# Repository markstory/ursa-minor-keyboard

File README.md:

# Ursa Minor Keyboard

This repository contains design and schematic files for the usra-minor keyboard design.

## Handwired

This directory contains the design files used to create the initial prototype of the tryptris keyboard.
You can find a design/build guide on my blog:

* [Part 1](http://mark-story.com/posts/view/building-a-split-keyboard-part-1)
* [Part 2](http://mark-story.com/posts/view/building-a-split-keyboard-part-2)
* [Part 3](http://mark-story.com/posts/view/building-a-split-keyboard-part-3)

## v01

This directory contains the first drafts of the PCB based build. I've completed
design on two variants. Both have been printed and tested. A few defects were
found in the `v01/bling` board. These defects have been corrected. I've posted
a [longer article on the design and production](http://mark-story.com/posts/view/designing-my-first-keyboard-pcb).

### Notable Features

* **Single MCU** - Instead of dual microcontrollers, this design uses only
  a microcontroller and IO expander pairing. This lets more cost effective
  components be used and only requires a single flash operation when updating
  firmware.
* **Thumb Arc** The thumb cluster follows the thumb's natural arc, and all keys
  are reachable in 1u of space. Unlike many thumb arcs, this one requires no
  reaching under the palm.
* **No Frills, or Frills** The base model has a simple stripped down keyboard.
  It has no lights, no encoders, just 58 switches and wires. The bling model
  includes support for per-key RGB.

### v01/base

**🖨Printed, ✅Tested**

This is a basic board design. It has has no frills and a smaller parts list. The intention is that it used caseless with self-adhesive feet, or directly on a desk.

### v01/bling

**🖨Printed, ✅Tested**

This design builds on caseless foundatin of the `v01/base` and adds per-key RGB lighting via RGB matrix drivers over I2C. Like the base board it is intended to be used caseless.

### v01/bling-case

**🏗Work In Progress**

This board is a distinct design from `v01/bling` & `v01/base`. It is intended to be used with a switch plate and hollow body case.

### Firmware

Firmware for the `v01/base` and `v01/bling` can be found [in my QMK fork][https://github.com/markstory/qmk_firmare/tree/ursa-minor-v1].

## FAQ

**Why Ursa Minor?**

The keypad shape and thumb arc remind me of [Ursa Minor](https://en.wikipedia.org/wiki/Ursa_Minor).

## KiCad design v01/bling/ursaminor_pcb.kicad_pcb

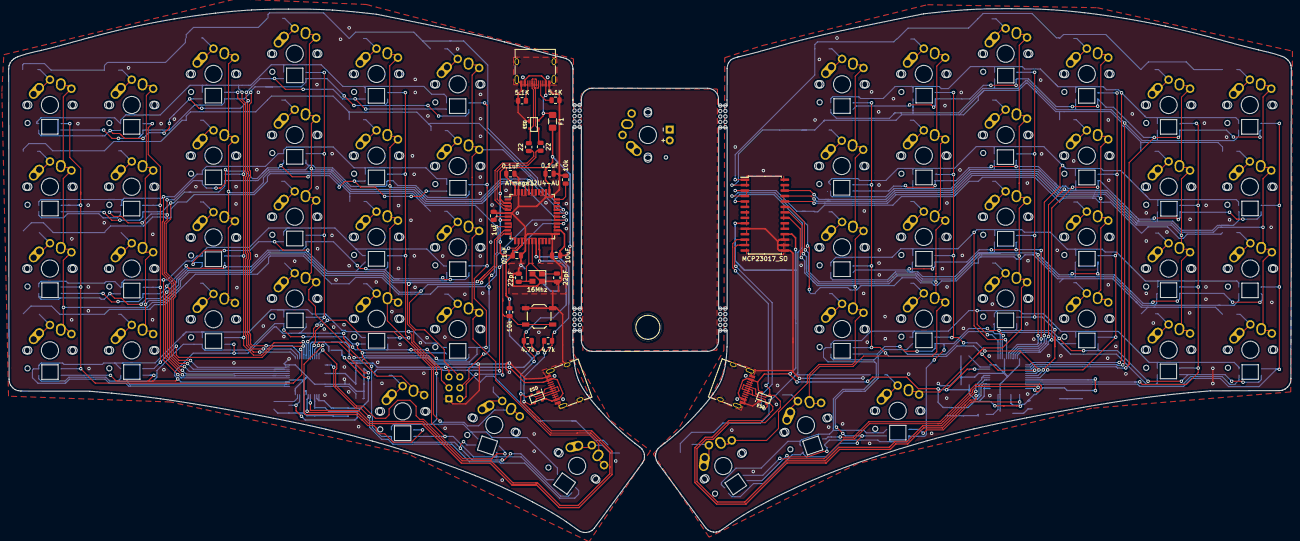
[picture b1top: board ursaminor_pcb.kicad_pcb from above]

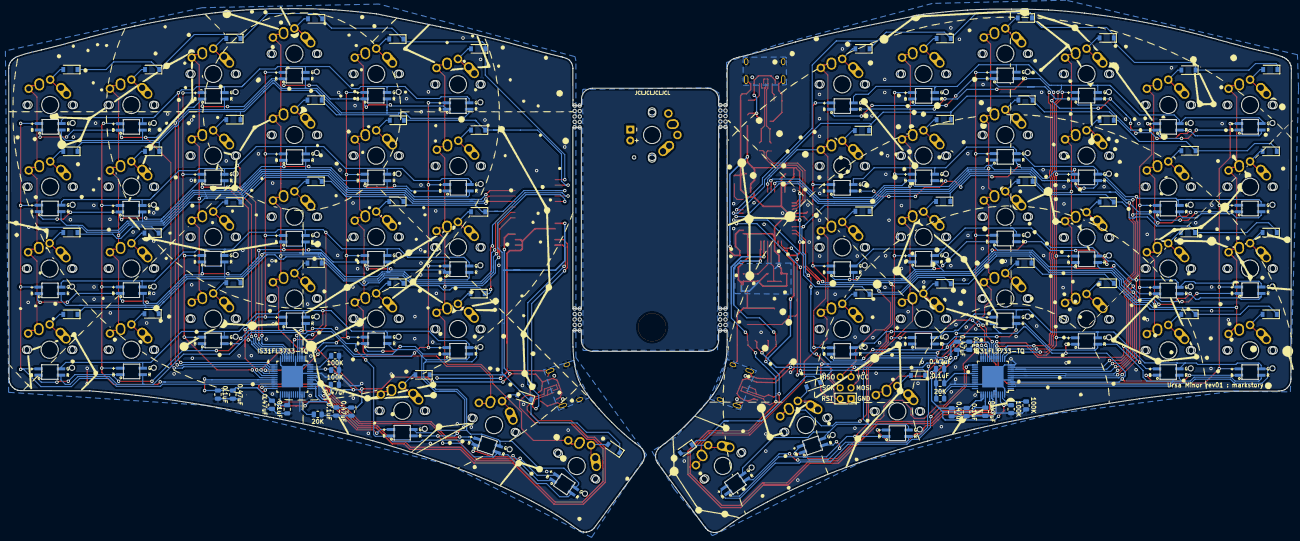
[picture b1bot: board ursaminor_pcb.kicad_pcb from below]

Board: 2 copper layers, 298.7 x 121.9 mm, 212 parts (131 on the bottom side), 142 nets.

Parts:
C1, C2: 22pF; C_0805_2012Metric
C3: 1uF; C_0805_2012Metric
C4, C5, C6, C14, C15, C16, C17, C18, C19: 0.1uF; C_0805_2012Metric
C7: 10uF; C_0805_2012Metric
C8, C9, C10, C11, C12, C13, C20, C21: 0.47uF; C_0805_2012Metric
D1, D2, D3, D4, D5, D6, D7, D8, D9, D10, D11, D12, D13, D14, D15, D16, D17, D18, D19, D20, D21, D22, D23, D24, D25, D26, D27, D28, D29, D30, D31, D32, D33, D34, D35, D36, D37, D38, D39, D40, D41, D42, D43, D44, D45, D46, D47, D48, D49, D50, D51, D52, D53, D54: 1N4148W; D_SOD-123
D55, D56, D57, D58, D59, D60, D61, D62, D63, D64, D65, D66, D67, D68, D69, D70, D71, D72, D73, D74, D75, D76, D77, D78, D79, D80, D81, D82, D83, D84, D85, D86, D87, D88, D89, D90, D91, D92, D93, D94, D95, D96, D97, D98, D99, D100, D101, D102, D103, D104, D105, D106, D107, D108: 6028 LED; RGB_3528_Blue_Notch-MX
F1: 500mA; Fuse_1206_3216Metric_Pad1.42x1.75mm_HandSolder
J1: USB_C_Receptacle_USB2.0; USB_C_Receptacle_HRO_TYPE-C-31-M-12
J2: I2C-L; USB_C_Receptacle_HRO_TYPE-C-31-M-12
J3: I2C-R; USB_C_Receptacle_HRO_TYPE-C-31-M-12
J4: AVR-ISP-6; Reset_Pretty-Mask
MX1: K0_0; MX-Alps-Choc-1U-NoLED
MX2: K0_1; MX-Alps-Choc-1U-NoLED
MX3: K0_2; MX-Alps-Choc-1U-NoLED
MX4: K0_3; MX-Alps-Choc-1U-NoLED
MX5: K0_4; MX-Alps-Choc-1U-NoLED
MX6: K0_5; MX-Alps-Choc-1U-NoLED
MX7: K1_0; MX-Alps-Choc-1U-NoLED
MX8: K1_1; MX-Alps-Choc-1U-NoLED
MX9: K1_2; MX-Alps-Choc-1U-NoLED
MX10: K1_3; MX-Alps-Choc-1U-NoLED
MX11: K1_4; MX-Alps-Choc-1U-NoLED
MX12: K1_5; MX-Alps-Choc-1U-NoLED
MX13: K2_0; MX-Alps-Choc-1U-NoLED
MX14: K2_1; MX-Alps-Choc-1U-NoLED
MX15: K2_2; MX-Alps-Choc-1U-NoLED
MX16: K2_3; MX-Alps-Choc-1U-NoLED
MX17: K2_4; MX-Alps-Choc-1U-NoLED
MX18: K2_5; MX-Alps-Choc-1U-NoLED
MX19: K3_0; MX-Alps-Choc-1U-NoLED
MX20: K3_1; MX-Alps-Choc-1U-NoLED
MX21: K3_2; MX-Alps-Choc-1U-NoLED
MX22: K3_3; MX-Alps-Choc-1U-NoLED
MX23: K3_4; MX-Alps-Choc-1U-NoLED
MX24: K3_5; MX-Alps-Choc-1U-NoLED
MX25: K4_3; MX-Alps-Choc-1U-NoLED
MX26: K4_4; MX-Alps-Choc-1U-NoLED
MX27: K4_5; MX-Alps-Choc-1U-NoLED
MX28: K0_6; MX-Alps-Choc-1U-NoLED
MX29: K0_7; MX-Alps-Choc-1U-NoLED
MX30: K0_8; MX-Alps-Choc-1U-NoLED
MX31: K0_9; MX-Alps-Choc-1U-NoLED
MX32: K0_10; MX-Alps-Choc-1U-NoLED
MX33: K0_11; MX-Alps-Choc-1U-NoLED
MX34: K1_6; MX-Alps-Choc-1U-NoLED
MX35: K1_7; MX-Alps-Choc-1U-NoLED
MX36: K1_8; MX-Alps-Choc-1U-NoLED
MX37: K1_9; MX-Alps-Choc-1U-NoLED
MX38: K1_10; MX-Alps-Choc-1U-NoLED
MX39: K1_11; MX-Alps-Choc-1U-NoLED
MX40: K2_6; MX-Alps-Choc-1U-NoLED
MX41: K2_7; MX-Alps-Choc-1U-NoLED
MX42: K2_8; MX-Alps-Choc-1U-NoLED
MX43: K2_9; MX-Alps-Choc-1U-NoLED
MX44: K2_10; MX-Alps-Choc-1U-NoLED
MX45: K2_11; MX-Alps-Choc-1U-NoLED
MX46: K3_6; MX-Alps-Choc-1U-NoLED
MX47: K3_7; MX-Alps-Choc-1U-NoLED
MX48: K3_8; MX-Alps-Choc-1U-NoLED
MX49: K3_9; MX-Alps-Choc-1U-NoLED
MX50: K3_10; MX-Alps-Choc-1U-NoLED
MX51: K3_11; MX-Alps-Choc-1U-NoLED
MX52: K4_6; MX-Alps-Choc-1U-NoLED
MX53: K4_7; MX-Alps-Choc-1U-NoLED
MX54: K4_8; MX-Alps-Choc-1U-NoLED
R1, R8: 10k; R_0805_2012Metric
R2, R3: 5.1K; R_0805_2012Metric
R4, R5: 22; R_0805_2012Metric
R6, R7: 4.7k; R_0805_2012Metric
R9, R10, R11, R12: 100K; R_0805_2012Metric
R13, R14: 20K; R_0805_2012Metric
SW1: Reset; SW_SPST_TL3342
U1: ATmega32U4-AU; TQFP-44_10x10mm_P0.8mm
U2: MCP23017_SO; SOIC-28W_7.5x17.9mm_P1.27mm
U3, U4#2: IS31FL3733-TQ; TQFP-48-1EP_7x7mm_P0.5mm_EP5x5mm
U4: HOLE; MountingHole
U5, U6, U7: PRTR5V0U2X; SOT-143B
Y1: 16Mhz; Crystal_SMD_3225-4Pin_3.2x2.5mm

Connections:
+5V: C4.1, C5.1, C6.1, C7.1, C11.2, C12.2, C13.1, C17.1, C18.2, C19.2, C21.2, F1.1, J2.A4, J2.A9, J2.B4, J2.B9, J4.2, R1.1, R6.2, R7.1, R11.1, U1.2, U1.7, U1.14, U1.24, U1.34, U1.44, U4#2.20, U4#2.29, U4#2.37, U4#2.38, U4#2.39, U4#2.46, U6.4
Col0: J4.1, MX1.1, MX7.1, MX13.1, MX19.1, U1.11
Col1: J4.4, MX2.1, MX8.1, MX14.1, MX20.1, U1.10
Col2: MX3.1, MX9.1, MX15.1, MX21.1, U1.28
Col3: MX4.1, MX10.1, MX16.1, MX22.1, MX25.1, U1.41
Col4: MX5.1, MX11.1, MX17.1, MX23.1, MX26.1, U1.40
Col5: MX6.1, MX12.1, MX18.1, MX24.1, MX27.1, U1.39
Col6: MX28.1, MX34.1, MX40.1, MX46.1, MX52.1, U2.21
Col7: MX29.1, MX35.1, MX41.1, MX47.1, MX53.1, U2.22
Col8: MX30.1, MX36.1, MX42.1, MX48.1, MX54.1, U2.23
Col9: MX31.1, MX37.1, MX43.1, MX49.1, U2.24
Col10: MX32.1, MX38.1, MX44.1, MX50.1, U2.25
Col11: MX33.1, MX39.1, MX45.1, MX51.1, U2.26
D+: R5.1, U1.4
D-: R4.2, U1.3
DN: J1.A7, J1.B7, R4.1, U5.3
DP: J1.A6, J1.B6, R5.2, U5.2
GND: C1.2, C2.2, C3.2, C4.2, C5.2, C6.2, C7.2, C11.1, C12.1, C13.2, C17.2, C18.1, C19.1, C21.1, J1.A1, J1.A12, J1.B1, J1.B12, J1.S1, J2.A1, J2.A12, J2.B1, J2.B12, J2.S1, J4.6, R2.1, R3.2, R8.1, R11.2, R12.2, R14.2, SW1.1, U1.5, U1.15, U1.23, U1.35, U1.43, U4#2.5, U4#2.12, U4#2.34, U4#2.43, U4#2.44, U4#2.48, U4#2.49, U5.1, U6.1, Y1.2, Y1.4
Left-CS1: D55.3, D67.3, D79.3, D91.3, U4#2.16
Left-CS2: D56.3, D68.3, D80.3, D92.3, U4#2.17
Left-CS3: D57.3, D69.3, D81.3, D93.3, U4#2.18
Left-CS4: D58.3, D70.3, D84.3, D94.3, U4#2.19
Left-CS5: D59.3, D71.3, D82.3, D95.3, U4#2.21
Left-CS6: D60.3, D72.3, D83.3, D96.3, U4#2.22
Left-CS7: D103.3, U4#2.23
Left-CS8: D104.3, U4#2.24
Left-CS9: D105.3, U4#2.25
Left-SW1: D91.4, D92.4, D93.4, D94.4, D95.4, D96.4, D103.4, D104.4, D105.4, U4#2.2
Left-SW2: D91.2, D92.2, D93.2, D94.2, D95.2, D96.2, D103.2, D104.2, D105.2, U4#2.3
Left-SW3: D91.1, D92.1, D93.1, D94.1, D95.1, D96.1, D103.1, D104.1, D105.1, U4#2.4
Left-SW4: D79.4, D80.4, D81.4, D82.4, D83.4, D84.4, U4#2.6
Left-SW5: D79.2, D80.2, D81.2, D82.2, D83.2, D84.2, U4#2.7
Left-SW6: D79.1, D80.1, D81.1, D82.1, D83.1, D84.1, U4#2.8
Left-SW7: D67.4, D68.4, D69.4, D70.4, D71.4, D72.4, U4#2.9
Left-SW8: D67.2, D68.2, D69.2, D70.2, D71.2, D72.2, U4#2.10
Left-SW9: D67.1, D68.1, D69.1, D70.1, D71.1, D72.1, U4#2.11
Left-SW10: D55.4, D56.4, D57.4, D58.4, D59.4, D60.4, U4#2.13
Left-SW11: D55.2, D56.2, D57.2, D58.2, D59.2, D60.2, U4#2.14
Left-SW12: D55.1, D56.1, D57.1, D58.1, D59.1, D60.1, U4#2.15
unnamed: C1.1, U1.17, Y1.1
unnamed: C2.1, U1.16, Y1.3
unnamed: C3.1, U1.6
unnamed: D1.2, MX1.2
unnamed: D2.2, MX2.2
unnamed: D3.2, MX3.2
unnamed: D4.2, MX4.2
unnamed: D5.2, MX5.2
unnamed: D6.2, MX6.2
unnamed: D7.2, MX7.2
unnamed: D8.2, MX8.2
unnamed: D9.2, MX9.2
unnamed: D10.2, MX10.2
unnamed: D11.2, MX11.2
unnamed: D12.2, MX12.2
unnamed: D13.2, MX13.2
unnamed: D14.2, MX14.2
unnamed: D15.2, MX15.2
unnamed: D16.2, MX16.2
unnamed: D17.2, MX17.2
unnamed: D18.2, MX18.2
unnamed: D19.2, MX19.2
unnamed: D20.2, MX20.2
unnamed: D21.2, MX21.2
unnamed: D22.2, MX22.2
unnamed: D23.2, MX23.2
unnamed: D24.2, MX24.2
unnamed: D25.2, MX25.2
unnamed: D26.2, MX26.2
unnamed: D27.2, MX27.2
unnamed: D28.2, MX28.2
unnamed: D29.2, MX29.2
unnamed: D30.2, MX30.2
unnamed: D31.2, MX31.2
unnamed: D32.2, MX32.2
unnamed: D33.2, MX33.2
unnamed: D34.2, MX34.2
unnamed: D35.2, MX35.2
unnamed: D36.2, MX36.2
unnamed: D37.2, MX37.2
unnamed: D38.2, MX38.2
unnamed: D39.2, MX39.2
unnamed: D40.2, MX40.2
unnamed: D41.2, MX41.2
unnamed: D42.2, MX42.2
unnamed: D43.2, MX43.2
unnamed: D44.2, MX44.2
unnamed: D45.2, MX45.2
unnamed: D46.2, MX46.2
unnamed: D47.2, MX47.2
unnamed: D48.2, MX48.2
unnamed: D49.2, MX49.2
unnamed: D50.2, MX50.2
unnamed: D51.2, MX51.2
unnamed: D52.2, MX52.2
unnamed: D53.2, MX53.2
unnamed: D54.2, MX54.2
unnamed: J1.A5, R2.2
unnamed: J1.B5, R3.1
unnamed: J4.5, R1.2, SW1.2, U1.13
unnamed: R8.2, U1.33
unnamed: R10.1, U3.47
unnamed: R12.1, U4#2.47
unnamed: R13.1, U3.35
unnamed: R14.1, U4#2.35
Right-CS1: D61.3, D73.3, D85.3, D97.3, U3.16
Right-CS2: D62.3, D74.3, D86.3, D98.3, U3.17
Right-CS3: D63.3, D75.3, D87.3, D99.3, U3.18
Right-CS4: D64.3, D76.3, D90.3, D100.3, U3.19
Right-CS5: D65.3, D77.3, D88.3, D101.3, U3.21
Right-CS6: D66.3, D78.3, D89.3, D102.3, U3.22
Right-CS7: D106.3, U3.23
Right-CS8: D107.3, U3.24
Right-CS9: D108.3, U3.25
Right-SW1: D97.4, D98.4, D99.4, D100.4, D101.4, D102.4, D106.4, D107.4, D108.4, U3.2
Right-SW2: D97.2, D98.2, D99.2, D100.2, D101.2, D102.2, D106.2, D107.2, D108.2, U3.3
Right-SW3: D97.1, D98.1, D99.1, D100.1, D101.1, D102.1, D106.1, D107.1, D108.1, U3.4
Right-SW4: D85.4, D86.4, D87.4, D88.4, D89.4, D90.4, U3.6
Right-SW5: D85.2, D86.2, D87.2, D88.2, D89.2, D90.2, U3.7
Right-SW6: D85.1, D86.1, D87.1, D88.1, D89.1, D90.1, U3.8
Right-SW7: D73.4, D74.4, D75.4, D76.4, D77.4, D78.4, U3.9
Right-SW8: D73.2, D74.2, D75.2, D76.2, D77.2, D78.2, U3.10
Right-SW9: D73.1, D74.1, D75.1, D76.1, D77.1, D78.1, U3.11
Right-SW10: D61.4, D62.4, D63.4, D64.4, D65.4, D66.4, U3.13
Right-SW11: D61.2, D62.2, D63.2, D64.2, D65.2, D66.2, U3.14
Right-SW12: D61.1, D62.1, D63.1, D64.1, D65.1, D66.1, U3.15
Row0-L: D1.1, D2.1, D3.1, D4.1, D5.1, D6.1, U1.30
Row0-R: D28.1, D29.1, D30.1, D31.1, D32.1, D33.1, U2.1
Row1-L: D7.1, D8.1, D9.1, D10.1, D11.1, D12.1, U1.29
Row1-R: D34.1, D35.1, D36.1, D37.1, D38.1, D39.1, U2.2
Row2-L: D13.1, D14.1, D15.1, D16.1, D17.1, D18.1, J4.3, U1.9
Row2-R: D40.1, D41.1, D42.1, D43.1, D44.1, D45.1, U2.3
Row3-L: D19.1, D20.1, D21.1, D22.1, D23.1, D24.1, U1.27
Row3-R: D46.1, D47.1, D48.1, D49.1, D50.1, D51.1, U2.4
Row4-L: D25.1, D26.1, D27.1, U1.26
Row4-R: D52.1, D53.1, D54.1, U2.5
SCL-L: J2.A7, J2.B7, R7.2, U1.18, U4#2.42, U6.3
SCL-R: J3.A7, J3.B7, U2.12, U3.42, U3.43, U7.3
SDA-L: J2.A6, J2.B6, R6.1, U1.19, U4#2.41, U6.2
SDA-R: J3.A6, J3.B6, U2.13, U3.41, U7.2
VBUS: C8.2, C9.2, C10.1, C14.1, C15.2, C16.2, C20.2, J3.A4, J3.A9, J3.B4, J3.B9, R9.1, U2.9, U2.18, U3.20, U3.29, U3.37, U3.38, U3.39, U3.46, U7.4
VCC: F1.2, J1.A4, J1.A9, J1.B4, J1.B9, U5.4
VSS: C8.1, C9.1, C10.2, C14.2, C15.1, C16.1, C20.1, J3.A1, J3.A12, J3.B1, J3.B12, J3.S1, R9.2, R10.2, R13.2, U2.10, U2.15, U2.16, U2.17, U3.5, U3.12, U3.34, U3.44, U3.48, U3.49, U7.1

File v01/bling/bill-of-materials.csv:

Id,Designator,Package,Quantity,Designation,Supplier,Part number,Price per,Total per board
3,"C16,C19,C18,C17,C15,C14,C6,C5,C4",C_0805_2012Metric,9,0.1uF,digikey,08053C104KAT2A,0.14,1.26
4,"U4,U3",TQFP-48-1EP_7x7mm_P0.5mm_EP5x5mm,2,IS31FL3733-TQ,digikey,IS31FL3733B-TQLS4-TR,4.94,9.88
5,"R14,R13",R_0805_2012Metric,2,20K,digikey,RMCF0805JT20K0,0.15,0.3
6,"R12,R11,R10,R9",R_0805_2012Metric,4,100K,digikey,RMCF0805JT100K,0.15,0.6
7,D1-54,RGB_3528_Blue_Notch-MX,54,6028 LED,aliexpress,/item/32834931333,0.122142857142857,6.59571428571429
8,"C21,C20,C13,C12,C11,C10,C9,C8",C_0805_2012Metric,8,0.47uF,digikey,CL21B474KOFNNNE,0.14,1.12
10,"R7,R6",R_0805_2012Metric,2,4.7k,digikey,ERJ-PB6B4701V,0.48,0.96
11,J3,USB_C_GCT_USB4085,1,I2C-R,mouser,USB4085-GF-A,1.28,1.28
12,J2,USB_C_GCT_USB4085,1,I2C-L,mouser,USB4085-GF-A,1.28,1.28
73,J1,USB_C_GCT_USB4085,1,USB_C_Receptacle_USB2.0,mouser,USB4085-GF-A,1.28,1.28
16,F1,Fuse_0805_2012Metric_Pad1.15x1.40mm_HandSolder,1,500mA,digikey,0ZCK0050FF2E,0.25,0.25
17,D1-54,D_SOD-123,54,1N4148W,digikey,1N4148W RHG,0.23,12.42
20,SW1,SW_SPST_TL3342,1,Reset,digikey,TL3342F160QG/TR,0.96,0.96
74,Y1,Crystal_SMD_3225-4Pin_3.2x2.5mm,1,16Mhz,digikey,ECS-160-8-33-RHN-TR,0.81,0.81
75,U2,SOIC-28W_7.5x17.9mm_P1.27mm,1,MCP23017_SO,mouser,579-MCP23017T-E/SO,1.92,1.92
76,U1,TQFP-44_10x10mm_P0.8mm,1,ATmega32U4-AU,digikey,ATMEGA32U4RC-AU,7.46,7.46
77,"R8,R1",R_0805_2012Metric,2,10k,digikey,RMCF0805JT10K0,0.15,0.3
78,"R5,R4",R_0805_2012Metric,2,22,digikey,RMCF0805FT22R0,0.15,0.3
79,"R3,R2",R_0805_2012Metric,2,5.1K,digikey,RMCF0805FT5K10,0.15,0.3
80,C7,C_0805_2012Metric,1,10uF,digikey,C0805C106K9PACTU,0.2,0.2
81,C3,C_0805_2012Metric,1,1uF,digikey,08056D104KAT2A,0.14,0.14
82,"C2,C1",C_0805_2012Metric,2,22pF,digikey,CL21A226MQQNNNE,0.2,0.4
,,,,,,,,50.0157142857143

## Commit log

2021-07-17 Add models and drawings for handwired prototype.
2021-07-17 Start schematic with MCU and left hand matrix
2021-07-18 Add right side components to schematics
    Still need to get a USBC port for the upstream connection.
    Not jazzed about using TRRS for the interconnects, but I need to figure
    out how USBC ports would work there. TRRS might be simpler given that
    this will be a PCB board.
2021-07-18 Revise schematic
    * Use a better USB connector schematic and footprint for a through-hole
    connector.
2021-07-18 Started left side of PCB
    * Got switches and diodes for the left side placed.
2021-07-22 PCB components roughly placed
    * Removed duplicate resistors on D- and D+
    * Roughly placed all components. MCU and IO expander and resistors are
    all on the back to save board space. I'm hoping that the board can fit
    inside the existing switch place outline.
2021-07-25 Made progress on the left side routing.
    I am going to put the components on the bottom (except diodes), and
    ports on the top so that the board can be lower to the table.
    A bunch of routing for the left side is done after a few different
    attempts.
2021-07-25 Add a licence and basic README
2021-07-26 Fiddle with wiring more.
2021-07-26 Move components to a block outside the switch matrix
    * Having the ports top mounted will let the board be lower profile.
    * Having the components on top looks kind of cool too.
    * Roughly routed the entire left sideci!
2021-07-26 Done first draft of right side wiring
2021-07-28 Fix missing connections and ground fill around crystal
2021-07-29 Fix ERC and DRC errors.
    Move right half to use VSS instead of GND and add power flags to remove
    net links between sides.
2021-07-29 Improve routing around crystal
    * I had scl and sda running under the crystal.
    * Fix 5v not going through decoupling capacitors.
2021-07-29 Improve USB data lines
    Reroute to get more equal lengths.
2021-08-01 Add panelization library for mousebites.
2021-08-01 Add center 'card' and mousebites.
    These help keep the board together. I'm thinking the card could
    either make several keychain items, or a small piece of art.
2021-08-01 Add label.
2021-08-02 Fix TRRS wiring and improve grounding
    * Don't route gnd for trrs through the crystal. Instead send it around the
    crystal and into the larger ground plane of the MCU.
    * Fix the right side wiring. 5V should pass through the resisitors
    before being connected to the signal wires. The goal is to provide
    background voltage not flood the signal.
2021-08-02 Start iterating on the back silkscreen image.
2021-08-04 Tweak routing, different back image and new submodules
    Try out some other back silkscreen images
2021-08-05 Finish rerouting for new switch footprints.
2021-08-05 Remove symbol libraries.
2021-08-12 Try a different back silkscreen image.
2021-08-14 Add first draft of 'keychain'
    Currently there are two keychain bits. I might go back to one though
    so the image can be larger.
2021-08-15 Revise center block more
    * Make solar model larger.
    * Shrink size of block so it fits on a keychain better.
    * Align items better.
    * Normalize width of edge cut lines.
2021-08-16 Remove unused edge cut files.
2021-08-16 Add constellation back silkscreens
    Considering renaming this project to one of the constellations so that
    everything fits thematically and putting the chosen constellation on the
    center block.
2021-08-22 Swap TRRS connectors out for USBC
    I have never been a big fan of TRRS and using USBC should be ok as I'm
    keeping the 5V and GND pins the same as with USB.
2021-08-22 Cleanup
2021-08-22 Add 3D models
    I had to hack up the gitmodules locally to point at the 3dmodels, I'll
    need to find a better way to do that.
2021-08-22 Update with 3d models and some small trace improvements.
2021-08-25 Put diodes on the bottom
    This lets the board top be much cleaner and there is no risk of the
    diodes impacting switches.
2021-08-27 Start schematics for RGB matrix.
    No idea if this is remotely correct. I will need to check my design
    against another design that uses the same RGB driver.
2021-08-28 Get RGB matrix roughed in.
2021-08-28 Fix ERC errors.
2021-08-28 Fix power sources.
2021-08-30 More routing progress on RGB matrix
2021-08-30 Finished rough routing the left side.
    Starting on the right.
2021-09-02 Finish first draft of routing on both sides.
2021-09-02 Tweak routing a bit.
2021-09-04 Move RGB design to a new directory
    I want to have the RGB and non RGB designs in the same branch.
2021-09-04 Import the base design in from master.
2021-09-04 Move name/author
2021-09-04 Consolidate shared graphical footprints
2021-09-04 Make paths more portable.
2021-09-04 Update README.
2021-09-04 Add sym directory.
2021-09-04 Add RGB specific silk screens
    Don't want to silkscreen over the RGB holes. Also remove some cruft.
2021-09-04 Remove redundant silk screen.
2021-09-04 Clean up base silk screen too.
2021-09-04 Add bill of materials files
2021-09-06 Move interconnect ports
    I got some feedback that they might be tight for some cables. By sliding
    the ports down a bit they can stay at the same angle and also give more
    space for cable housing.
2021-09-06 Move RGB LED footprint to a local lib
    I don't want as much content on the silkscreen.
2021-09-08 Add mounting holes to bling.
2021-09-08 Make schematic clearer
    * Improve routing around mounting holes
    * Fix all DRC errors.
2021-09-14 Update bill of materials with vendors and part numbers.
    Tweak more routing as well.
2021-09-19 Update base model to use parts from lcsc
    The footprints for USB ports had to change as I can't get the previous
    footprint shape from lcsc.
2021-09-19 Tidy up silkscreen.
2021-09-21 Use freeform routing to get USB ports in a better position.
2021-09-23 Move I2C resistors to the left side for bling
    This should ensure that the LED drivers on the left side work correctly
    when the right side is not plugged in.
2021-09-23 Move I2C resistors to MCU side
    This lets the right side be simpler and visually cleaner. It also
    matches the component layout of the bling version.
2021-09-25 Add ISP connector to base board.
2021-09-25 Add ISP port to the bling board.
2021-09-28 Fix ISP wiring
    I got the pins wrong.
2021-09-28 Fix ISP connection and move mounting holes
    I had the pins wrong. Top mounting holes are more equal in height and
    evenly spread around the board.
2021-09-28 Update README a bit.
2021-10-02 Add ESD component to both boards.
2021-10-02 Fix stray trace.
2021-10-04 Tweak routing more.
2021-10-04 Tweak routing on bling and add copper fill on left side
2021-10-04 Add more copper fill
2021-10-05 Improve fill areas for bling.
2021-10-05 Add copper fills to base.
2021-10-09 Add interconnect ESD to base.
2021-10-09 Add ESD circuits to bling interconnects.
2021-10-26 Rename project.
2021-10-26 Rename files and update path references.
2021-10-26 Fix DRC and add jcl tag
2021-10-26 Ignore gerbers.
2021-10-26 More plotting fixes.
2021-10-28 Remove silkscreen from contacts and pad.
2021-10-29 Update silkscreen
2021-10-30 Use 5mm mousebites instead
    The reveiwers at JLCPCB requested wider mousebites as 2mm
    ones are 'too small'.
2021-10-30 Update cache
2021-10-31 Add drawing of board outline.
2021-11-01 Update footprints
2022-01-23 Fix LED driver wiring
    - Caps were not in ordered as per the docs. This doesn't matter *too*
    much but it is nice to be more correct.
    - IS31FL3733 needs SDB set high to ensure the chip is always on.
    Previously it was pulled low causing the chip to shut off.
2022-01-24 Remove stray trace and fix fill zones
    Found some problems in the printed boards.
2022-01-24 Tweak routing to improve fill areas
    Found some gaps on the printed boards that could be filled.
2022-02-08 Update readme
    Firmware is published now.
2022-02-25 Fix incorrectly wired ESD
2022-02-25 Update README and add new board.
2022-02-25 Add copy-paste from bling board.
2022-02-25 Start working on bling-base
    * Use north face LEDS as south facing ones have a tendency to shine in
    my eyes.
    * Import the board outline from onshape.
2022-02-27 Get left side components placed
    Routing is going to be tricky but it still seems doable.
2022-03-02 Improve component layout and start routing traces.
2022-03-06 More routing on the left side
2022-03-09 Get RGB matrix on left side roughly routed
    If I can get the left side to work, the right should be easier.
2022-03-16 More routing progress.
2022-03-19 Routing MCU and LED driver
    * Roughly finished on the MCU. I think components are still close to the
    required pins.
    * Starting to routes traces out of LED driver to the matrix lines. I had
    to rotate the driver and this caused a relayout of the surrounding
    area.
2022-03-23 Almost done routing the left side.
2022-03-24 Get left side routed.
2022-03-27 Clean up right side and roughly place components.
    Still need to figure out the right side LED driver.
2022-03-28 First draft of complete right side placements
2022-03-28 Top row of right LEDs and LED columns are done.
2022-04-02 Complete more routing on the right side.
2022-04-03 Route the data lines and some of the RGB matrix on the right side.
2022-04-04 More routing on the right side.
2022-04-07 Route more of the right side.
2022-04-09 Finished routing and via stitching the gnd planes together.
2022-04-10 Remove mounting holes as they didn't end up working
2022-04-11 Fix DRC errors.
2022-04-11 Reduce area used and fix outline and DRC
2022-04-13 Make fancier
2022-04-13 Add blog link
2022-04-15 Add silkscreen to top and adjust bottom silkscreen.
